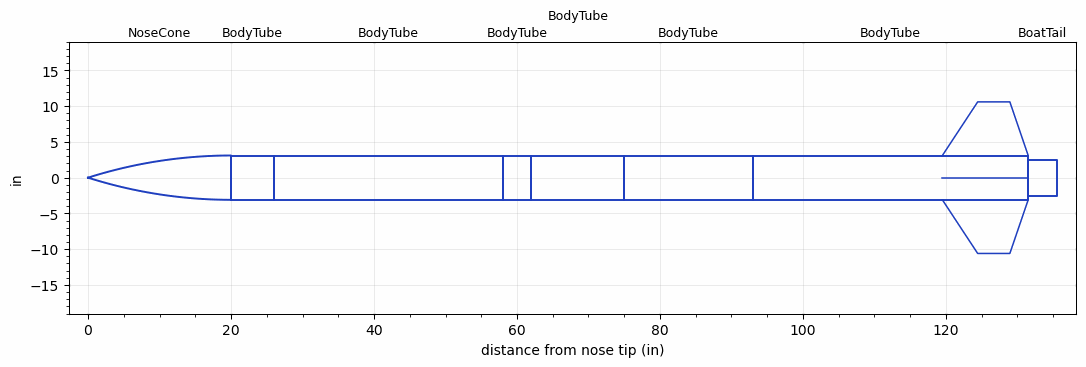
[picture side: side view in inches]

<RASAeroDocument>
 <FileVersion>2</FileVersion>
 <RocketDesign>
  <NoseCone>
   <Length>20</Length>
   <Diameter>6.2</Diameter>
   <Shape>Tangent Ogive</Shape>
   <Location>0</Location>
  </NoseCone>
  <BodyTube>
   <Length>6</Length>
   <Diameter>6.2</Diameter>
   <Location>20</Location>
  </BodyTube>
  <BodyTube>
   <Length>31.9999</Length>
   <Diameter>6.2</Diameter>
   <Location>25.9999</Location>
  </BodyTube>
  <BodyTube>
   <Length>4</Length>
   <Diameter>6.2</Diameter>
   <Location>57.9999</Location>
  </BodyTube>
  <BodyTube>
   <Length>13</Length>
   <Diameter>6.2</Diameter>
   <Location>61.9999</Location>
  </BodyTube>
  <BodyTube>
   <Length>18</Length>
   <Diameter>6.2</Diameter>
   <Location>74.9998</Location>
  </BodyTube>
  <BodyTube>
   <Length>38.4999</Length>
   <Diameter>6.2</Diameter>
   <RailGuideDiameter>0.621</RailGuideDiameter>
   <RailGuideHeight>0.6845</RailGuideHeight>
   <Location>92.9998</Location>
   <Fin>
    <Count>4</Count>
    <Chord>12</Chord>
    <Span>7.5</Span>
    <SweepDistance>4.937</SweepDistance>
    <TipChord>4.5</TipChord>
    <Thickness>0.125</Thickness>
    <Location>12</Location>
    <AirfoilSection>Rounded</AirfoilSection>
   </Fin>
  </BodyTube>
  <BoatTail>
   <Length>4</Length>
   <Diameter>5</Diameter>
   <RearDiameter>5</RearDiameter>
   <Location>131.4997</Location>
  </BoatTail>
  <Surface>Sheet Metal</Surface>
  <CD>0</CD>
  <ModifiedBarrowman>False</ModifiedBarrowman>
  <Turbulence>False</Turbulence>
  <UseBooster1>False</UseBooster1>
  <UseBooster2>False</UseBooster2>
 </RocketDesign>
 <LaunchSite>
  <Altitude>2870.735</Altitude>
  <Pressure>26.9525</Pressure>
  <RodAngle>5</RodAngle>
  <RodLength>163.9997</RodLength>
  <Temperature>48.7625</Temperature>
  <WindSpeed>15</WindSpeed>
 </LaunchSite>
 <Recovery>
  <Altitude1>1476.378</Altitude1>
  <Altitude2>656.168</Altitude2>
  <DeviceType1>Parachute</DeviceType1>
  <DeviceType2>Parachute</DeviceType2>
  <Event1>True</Event1>
  <Event2>True</Event2>
  <Size1>95.9998</Size1>
  <Size2>35.9999</Size2>
  <EventType1>Altitude</EventType1>
  <EventType2>Apogee</EventType2>
  <CD1>2</CD1>
  <CD2>0</CD2>
 </Recovery>
 <SimulationList>
  <Simulation>
   <SustainerEngine>N3800-LW  (LR)</SustainerEngine>
   <SustainerLaunchWt>91.6657</SustainerLaunchWt>
   <SustainerCG>84.5355</SustainerCG>
   <SustainerIgnitionDelay>0</SustainerIgnitionDelay>
   <Booster1SeparationDelay>0</Booster1SeparationDelay>
   <Booster1IgnitionDelay>0</Booster1IgnitionDelay>
   <IncludeBooster1>False</IncludeBooster1>
   <Booster2Delay>0</Booster2Delay>
   <IncludeBooster2>False</IncludeBooster2>
  </Simulation>
 </SimulationList>
</RASAeroDocument>
